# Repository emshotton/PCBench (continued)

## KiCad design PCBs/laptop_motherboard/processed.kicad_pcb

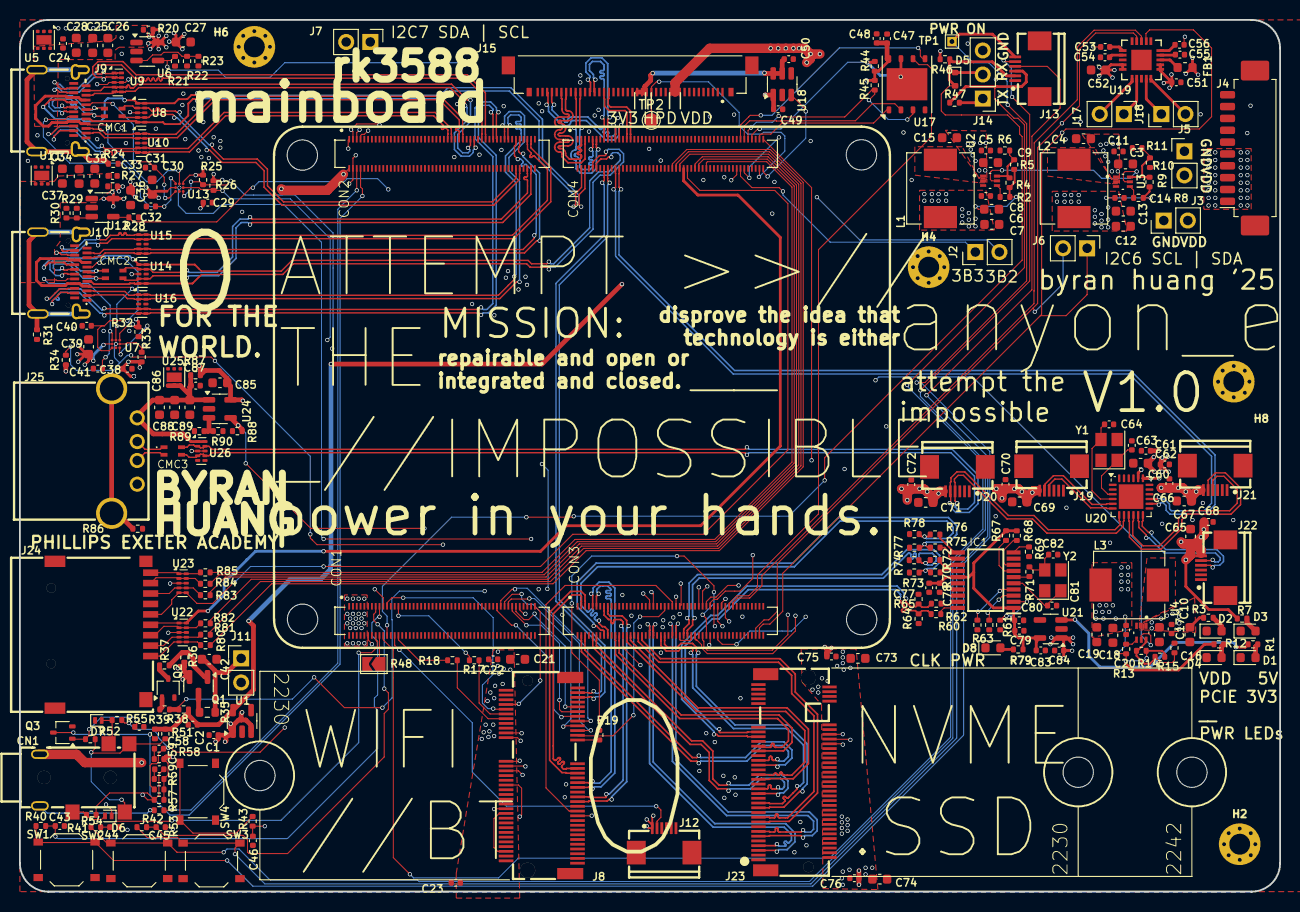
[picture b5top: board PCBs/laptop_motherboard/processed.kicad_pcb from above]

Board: 6 copper layers, 133.0 x 92.0 mm, 264 parts (0 on the bottom side), 236 nets.

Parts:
C1, C2, C22, C48, C49, C50, C53, C54, C55, C56, C57, C62, C75, C77, C79, C83, C84: 1uF; C_0402_1005Metric
C3, C4, C9, C10, C15, C16, C27, C28, C30, C36, C37, C39, C42, C52, C60, C65, C67, C69, C71, C85, C86: 10uF; C_0603_1608Metric
C5, C8, C11, C14, C17, C20, C29, C38, C78, C80: 100nF; C_0402_1005Metric
C6, C7, C12, C13, C18, C19, C21, C73, C74: 22uF; C_0603_1608Metric
C23, C47, C51, C58, C59, C61, C66, C68, C70, C72, C76: 0.1uF; C_0402_1005Metric
C24, C33, C87: 100nF (+25V); C_0402_1005Metric
C25, C26, C34, C35, C88, C89: 10uF (C913517); C_0603_1608Metric
C31, C32, C40, C41: 220pF; C_0402_1005Metric
C43, C44, C45, C46: 1nF; C_0402_1005Metric
C63, C64, C81, C82: 15pF; C_0402_1005Metric
CMC1, CMC2, CMC3: ACM2012; FIL_ACM2012-900-2P-T001
CN1: PJ-332A-6A (3.5mm Jack); AUDIO-SMD_PJ-332A-6A
D1: +3.3V LED; LED_0603_1608Metric
D2: VDD LED; LED_0603_1608Metric
D3: +5V LED; LED_0603_1608Metric
D4: PCIE LED; LED_0603_1608Metric
D5: LRB521S-30T1G; D_SOD-523
D6, D7: LESD8D5.0CB1T5G; D_SOD-882
D8: PI6C LED; LED_0603_1608Metric
FB1: GZ1608D601TF; L_0603_1608Metric
H1, H3, H5, H7: Hirose; Blank
H2, H4, H6, H8: M2; MountingHole_2.2mm_M2_Pad_Via
IC1: PI6C557-05BLE; SOP65P640X120-20N
J1: CM3588 Hirose Connector; CM3588
J2, J6, J7: EXT GPIO; PinHeader_1x02_P2.54mm_Vertical
J3: VDD EXT; PinHeader_1x02_P2.54mm_Vertical
J4: BATTERY IN; Molex_PicoBlade_53261-1071_1x10-1MP_P1.25mm_Horizontal
J5: VDD EXT 2; PinHeader_1x02_P2.54mm_Vertical
J8: Bus_M.2_Socket_E; CONN-SMD_APCI0147-P001A
J9: Outer USB-C; USB-C-SMD_TYPE-C-24P-QT
J10: USB_C_Receptacle; USB-C-SMD_TYPE-C-24P-QT
J11: 5V FAN; PinHeader_1x02_P2.54mm_Vertical
J12: HALL SWITCH; FPC-SMD_6P-P0.50_XUNPU_FPC-05F-6PH20
J13: SYSTEM; FPC-SMD_6P-P0.50_XUNPU_FPC-05F-6PH20
J14: DEBUG UART; PinHeader_1x03_P2.54mm_Vertical
J15: 20455-040E-76 OLED IPEX; IPEX_20455-040E-76
J17: LEFT SPEAKERS; PinHeader_1x02_P2.54mm_Vertical
J18: RIGHT SPEAKERS; PinHeader_1x02_P2.54mm_Vertical
J19, J20, J21, J22: USB; FPC-SMD_6P-P0.50_XUNPU_FPC-05F-6PH20
J23: Bus_M.2_Socket_M; CONN-SMD_AS0BC21-S30BM-7H
J24: Micro_SD_Card_Det1; TF-SMD_TF-CARD-H1.8
J25: USB-231-ARY; USB-A-TH_USB-231-ARY
L1, L3: MWSA0603S-3R3MT; L_Sunlord_MWSA0603S
L2: FXL0630-4R7-M; L_Sunlord_MWSA0603S
Q1: AO3415A; SOT-23
Q2, Q3: 2SK3018W; SOT-323_SC-70
R1, R2, R6, R7, R8, R12, R13, R16, R34, R38, R44, R45, R46, R52, R56, R57, R67, R68: 10k; R_0402_1005Metric
R3, R11, R79: 33k; R_0402_1005Metric
R4, R14: 49.9k; R_0402_1005Metric
R5, R15: 510k; R_0402_1005Metric
R9: 220k; R_0402_1005Metric
R10: 330k; R_0402_1005Metric
R17, R18, R20, R27, R53, R54, R55, R61, R63, R87: 0R; R_0402_1005Metric
R19, R25, R26, R32, R33, R50: 2.2k; R_0402_1005Metric
R21, R28, R51, R88: 100k; R_0402_1005Metric
R22, R23, R29, R30, R89, R90: 6.8k; R_0402_1005Metric
R24, R31, R86: 1M; R_0402_1005Metric
R35: 2.2R; R_0603_1608Metric
R36, R69: 470R; R_0402_1005Metric
R37: 1k; R_0402_1005Metric
R39, R40, R41, R42, R43, R71: 100R; R_0402_1005Metric
R47, R58, R59, R60, R62, R70, R72, R75, R76, R80, R81, R82, R83, R84, R85: 33R; R_0402_1005Metric
R48: 0R; SolderJumper-2_P1.3mm_Open_TrianglePad1.0x1.5mm
R64, R65, R73, R74, R77, R78: 49.9R; R_0402_1005Metric
R66: 4.7k; R_0402_1005Metric
SW1: PWR; SW_Push_1P1T_XKB_TS-1187A
SW2: RESET; SW_Push_1P1T_XKB_TS-1187A
SW3: MASK; SW_Push_1P1T_XKB_TS-1187A
SW4: RECOVERY; SW_Push_1P1T_XKB_TS-1187A
TP1: PWRON; TestPoint_THTPad_1.0x1.0mm_Drill0.5mm
TP2: HPD; TestPoint_Pad_D1.5mm
U1: RT9193-18GB; SOT-23-5
U2, U3, U4: TPS564257DRLR; SOT50P160X60-6N
U5, U11, U25: TVS2200DRV; WSON-6-1EP_2x2mm_P0.65mm_EP1x1.6mm
U6, U12, U24: SY6280AAC; SOT-23-5
U7, U13: FUSB302BUCX; WLCSP9_1P2X1P2_ONS
U8, U9, U10, U14, U15, U16, U22, U23, U26: TPD4E02B04; USON-10_2.5x1.0mm_P0.5mm
U17: SPI Flash; WSON-8-1EP_6x5mm_P1.27mm_EP3.4x4.3mm
U18: TPS22917DBV; SOT-23-6
U19: TPA2016D2RTJR; QFN50P400X400X80-21N
U20: CH334F; QFN-24-1EP_4x4mm_P0.5mm_EP2.6x2.6mm
U21: AP2127K-3.3; SOT-23-5
Y1: 12MHz; Crystal_SMD_3225-4Pin_3.2x2.5mm
Y2: 25MHz; Crystal_SMD_3225-4Pin_3.2x2.5mm

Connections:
+1V8: C2.1, C47.1, C48.1, R38.1, R44.1, R45.1, R50.2, R51.2, U1.5 (VOUT), U17.8 (VCC)
+3.3V: C1.1, C6.1, C7.1, C8.1, C29.1, C38.1, C49.1, C60.1, C61.1, L1.2, R1.2, R2.2, R4.2, R5.2, R25.1, R26.1, R32.1, R33.1, R34.1, R46.2, U1.1 (VIN), U1.3 (EN), U7.A3 (VDD), U13.A3 (VDD), U18.1 (VIN), U20.20 (VDD33), U21.3 (EN)
+3.3V_PCIE: C18.1, C19.1, C20.1, C21.1, C22.1, C23.1, C73.1, C74.1, C75.1, C76.1, J8.2 (3.3V), J8.4 (3.3V), J8.72 (3.3V), J8.74 (3.3V), J12.1, J23.2 (3.3V), J23.4 (3.3V), J23.12 (3.3V), J23.14 (3.3V), J23.16 (3.3V), J23.18 (3.3V), J23.70 (3.3V), J23.72 (3.3V), J23.74 (3.3V), L3.2, R12.2, R13.2, R14.2, R15.2
+5V: C12.1, C13.1, C14.1, C27.1, C30.1, C36.1, C39.1, C51.1, C52.1, C62.1, C65.1, C66.1, C67.1, C68.1, C69.1, C70.1, C71.1, C72.1, C84.1, C85.1, FB1.1, J19.6, J20.6, J21.6, J22.6, L2.2, Q1.2 (S), R7.2, R8.2, R9.2, R20.1, R27.1, R36.1, R87.1, U6.5 (IN), U7.B1 (VCONN), U12.5 (IN), U13.B1 (VCONN), U19.4 (PVDDL_2), U19.5 (PVDDL), U19.11 (PVDDR_2), U19.12 (PVDDR), U20.19 (V5), U21.1 (VIN), U24.5 (IN)
/3V3_SW: L1.1, U2.2 (SW)
/5V_SW: L2.1, U3.2 (SW)
/Audio/L_AUDIO: C53.1, C58.1, J1.104, R55.2, R56.2
/Audio/L_DET: CN1.5, CN1.6, R51.1, R52.2
/Audio/L_HP: CN1.4, D7.2 (A2), R55.1
/Audio/MIC: CN1.1, R53.1
/Audio/R_AUDIO: C56.1, C59.1, J1.103, R54.2, R57.2
/Audio/R_HP: CN1.3, D6.2 (A2), R54.1
/BOOT_SARADC_IN0: C45.1, J1.15, R42.1
/Ext_USB2.0/EXTUSB20_D3_N: CMC3.4, J20.5, U26.2 (D1-), U26.9 (NC)
/Ext_USB2.0/EXTUSB20_D3_P: CMC3.3, J20.4, U26.4 (D2+), U26.7 (NC)
/Ext_USB2.0/USB_N: CMC3.1, J25.2 (D-)
/Ext_USB2.0/USB_P: CMC3.2, J25.3 (D+)
/Ext_USB2.0/VBUS: C86.1, C87.1, C88.1, C89.1, J25.1 (VBUS), R87.2, U24.1 (OUT), U25.4 (IN), U25.5 (IN), U25.6 (IN), U26.1 (D1+), U26.10 (NC)
/GPIO0_A4/SDMMC_DET_L: J1.370, R85.1
/GPIO0_B2: J1.247, J8.21 (~SDIO_WAKE)
/GPIO0_C4/UART0_RX_M0: J1.270, R19.1
/GPIO0_C5/UART0_TX_M0/PWM4_M0: J1.272, J8.20 (~UART_WAKE)
/GPIO0_D3/CC_INT_L: J1.264, U13.B2 (INT_N)
/GPIO0_D5: J1.268, R34.2, U7.B2 (INT_N)
/GPIO1_A0/UART6_RX_M1: J1.273, J8.22 (UART_RXD)
/GPIO1_A1/UART6_TX_M1: J1.275, J8.32 (UART_TXD)
/GPIO1_A2/I2C4_SDA_M3_TP: J1.277, J8.36 (UART_RTS)
/GPIO1_A3/I2C4_SCL_M3_TP: J1.279, J8.34 (UART_CTS)
/GPIO1_A4: J1.281, U17.6 (SCK)
/GPIO1_A7: J1.283, U19.18 (SDZ)
/GPIO1_B0: J1.276, R88.1, U24.4 (ON)
/GPIO1_C4/HP_DET_L: J1.108, Q3.3 (D), R50.1
/GPIO1_D2/TYPEC5V_PWREN_H: J1.239, R21.1, U6.4 (ON)
/GPIO1_D3/PWM1_M1: J1.241, R38.2, R39.1
/GPIO2_A6: J1.79, J8.13 (SDIO_DATA0)
/GPIO2_A7: J1.81, J8.15 (SDIO_DATA1)
/GPIO2_B0: J1.83, J8.17 (SDIO_DATA2)
/GPIO2_B1: J1.85, J8.19 (SDIO_DATA3)
/GPIO2_B2: J1.87, J8.11 (SDIO_CMD)
/GPIO2_B3: J1.89, J8.9 (SDIO_CLK)
/GPIO2_B7: J1.99, J8.8 (PCM_CLK/I2S_SCK)
/GPIO2_C0: J1.21, J8.10 (PCM_SYNC/I2S_WS)
/GPIO2_C3: J1.27, R17.2
/GPIO3_A0/SPI4_MISO_M1/PWM10_M0: J1.387, U17.5 (SI/IO0)
/GPIO3_A1/SPI4_MOSI_M1: J1.389, U17.2 (SO/IO1)
/GPIO3_A2/SPI4_CLK_M1/UART8_TX_M1: J1.391, R45.2, U17.3 (~WP/IO2)
/GPIO3_A3/SPI4_CS0_M1/UART8_RX_M1: J1.393, R44.2, U17.7 (~HOLD/IO3)
/GPIO3_A5: J1.397, U17.1 (~CS)
/GPIO3_A6/LCD_RST: J1.399, J8.42 (VENDOR_DEFINED)
/GPIO3_A7: J1.400, U18.3 (ON)
/GPIO3_B2: J1.386, J2.2
/GPIO3_B3: J1.388, J2.1
/GPIO3_B4: J1.390, R28.1, U12.4 (ON)
/GPIO3_B7: J1.398, J15.16, TP2.1
/GPIO4_A0/TP_2_INT_L: J1.251, J8.53 (~CLKREQ0)
/GPIO4_A1/TP_2_RST_L: J1.253, J8.55 (~PEWAKE0)
/GPIO4_A2: J1.255, J8.52 (~PERST0)
/GPIO4_B4/PCIE30X4_CLKREQn_M1_L: J1.265, J23.52 (~CLKREQ)
/GPIO4_B5/PCIE30X4_WAKEn_M1_L: J1.267, J23.54 (~PEWAKE)
/GPIO4_B6/PCIE30X4_PERSTn_M1_L: J1.269, J23.50 (~PERST)
/GPIO4_C2: J1.26, J12.2
/GPIO4_C3: J1.28, R18.2
/HDMI1_TX0N: J1.317, J15.29
/HDMI1_TX0P: J1.315, J15.28
/HDMI1_TX1N: J1.311, J15.32
/HDMI1_TX1P: J1.309, J15.31
/HDMI1_TX2N: J1.305, J15.35
/HDMI1_TX2P: J1.303, J15.34
/HDMI1_TX3N: J1.323, J15.38
/HDMI1_TX3P: J1.321, J15.37
/HDMI1_TX_SBDN: J1.329, J15.25
/HDMI1_TX_SBDP: J1.327, J15.26
/I2C6_SCL_M0: J1.296, J6.2, R26.2, U13.B3 (SCL), U19.19 (SDA)
/I2C6_SDA_M0: J1.298, J6.1, R25.2, U13.C3 (SDA), U19.17 (SCL)
/I2C7_SCL_M0: J1.107, J7.1, R33.2, U7.B3 (SCL)
/I2C7_SDA_M0: J1.105, J7.2, R32.2, U7.C3 (SDA)
/MIC_IN: J1.106, R53.2
/PCIE2.0-EKEY/GPIO3_D5/PWM11_M3/LCD_2_BL: J8.54 (~W_DISABLE2), J8.70 (UIM_POWER_SRC/GPIO1/~PEWAKE1)
/PCIE3.0-MKEY/+3.3V_PI6C: C77.1, C78.1, C79.1, C80.1, C83.1, IC1.1 (VDDXD), IC1.15 (VDDODA), R67.1, R68.1, R79.2, U21.5 (VOUT)
/PCIE3.0-MKEY/CLK2N: IC1.13 (~CLK2), R72.1
/PCIE3.0-MKEY/CLK2P: IC1.14 (CLK2), R70.1
/PCIE3.0-MKEY/CLK3N: IC1.11 (~CLK3), R76.1
/PCIE3.0-MKEY/CLK3P: IC1.12 (CLK3), R75.1
/PCIE3.0-MKEY/PCIE30_REFCLK_A_N: J23.53 (REFCLKn), R62.2, R65.2
/PCIE3.0-MKEY/PCIE30_REFCLK_A_P: J23.55 (REFCLKp), R60.2, R64.2
/PCIE3.0-MKEY/X1: C81.1, IC1.5 (X1), Y2.1
/PCIE3.0-MKEY/X2: IC1.6 (X2), R71.1
/PCIE20_1_REFCLKN: J1.217, J8.49 (REFCLKn0)
/PCIE20_1_REFCLKP: J1.215, J8.47 (REFCLKp0)
/PCIE20_1_RXN: J1.211, J8.41 (PERp0)
/PCIE20_1_RXP: J1.209, J8.43 (PERn0)
/PCIE20_1_TXN: J1.205, J8.37 (PETn0)
/PCIE20_1_TXP: J1.203, J8.35 (PETp0)
/PCIE30_PORT0_REFCLKN: J1.218, R76.2, R78.2
/PCIE30_PORT0_REFCLKP: J1.216, R75.2, R77.2
/PCIE30_PORT0_RX0N: J1.206, J23.41 (PERn0/SATA-B+)
/PCIE30_PORT0_RX0P: J1.204, J23.43 (PERp0/SATA-B-)
/PCIE30_PORT0_RX1N: J1.212, J23.29 (PERn1)
/PCIE30_PORT0_RX1P: J1.210, J23.31 (PERp1)
/PCIE30_PORT0_TX0N: J1.224, J23.47 (PETn0/SATA-A-)
/PCIE30_PORT0_TX0P: J1.222, J23.49 (PETp0/SATA-A+)
/PCIE30_PORT0_TX1N: J1.230, J23.35 (PETn1)
/PCIE30_PORT0_TX1P: J1.228, J23.37 (PETp1)
/PCIE30_PORT1_REFCLKN: J1.260, R72.2, R74.2
/PCIE30_PORT1_REFCLKP: J1.258, R70.2, R73.2
/PCIE30_PORT1_RX2N: J1.236, J23.17 (PERn2)
/PCIE30_PORT1_RX2P: J1.234, J23.19 (PERp2)
/PCIE30_PORT1_RX3N: J1.242, J23.5 (PERn3)
/PCIE30_PORT1_RX3P: J1.240, J23.7 (PERp3)
/PCIE30_PORT1_TX2N: J1.248, J23.23 (PETn2)
/PCIE30_PORT1_TX2P: J1.246, J23.25 (PETp2)
/PCIE30_PORT1_TX3N: J1.254, J23.11 (PETn3)
/PCIE30_PORT1_TX3P: J1.252, J23.13 (PETp3)
/PCIE_SW: L3.1, U4.2 (SW)
/PMIC_EXT_EN_OUT: J1.19, U2.5 (EN), U3.5 (EN), U4.5 (EN)
/PWRON_L: C43.1, J1.17, R40.1
/RECOVERY: C46.1, J1.101, R43.1
/RESET_L: C44.1, J1.16, R41.1
/SD Card/CLK: J1.360, J24.5 (CLK), U23.5 (D2-), U23.6 (NC)
/SD Card/CMD: J24.3 (CMD), R82.2, U22.2 (D1-), U22.9 (NC)
/SD Card/D0: J24.7 (DAT0), R83.2, U23.4 (D2+), U23.7 (NC)
/SD Card/D1: J24.8 (DAT1), R84.2, U23.2 (D1-), U23.9 (NC)
/SD Card/D2: J24.1 (DAT2), R80.2, U22.5 (D2-), U22.6 (NC)
/SD Card/D3: J24.2 (DAT3/CD), R81.2, U22.4 (D2+), U22.7 (NC)
/SD Card/DET: J24.9 (DET), R85.2, U23.1 (D1+), U23.10 (NC)
/SD Card/VDD: J1.358, J24.4 (VDD), U22.1 (D1+), U22.10 (NC)
/SDMMC0_CMD: J1.356, R82.1
/SDMMC0_D0: J1.364, R83.1
/SDMMC0_D1: J1.366, R84.1
/SDMMC0_D2: J1.352, R80.1
/SDMMC0_D3: J1.354, R81.1
/System/BOOT_SARADC: J13.4, R42.2, SW3.1 (A)
/System/PWRON_L_IN: J13.6, R40.2, SW1.1 (A), TP1.1
/System/RECOVERY_IN: R43.2, SW4.1 (A)
/System/RESET_L_IN: J13.5, R41.2, SW2.1 (A)
/System/UART_RX: D5.2 (A), J1.22, J13.2, R46.1
/System/UART_TX: J1.20, J13.3, R47.1
/USB2.0/D1_N: J22.5, U20.11 (DM1)
/USB2.0/D1_P: J22.4, U20.12 (DP1)
/USB2.0/D2_N: J21.5, U20.9 (DM2)
/USB2.0/D2_P: J21.4, U20.10 (DP2)
/USB2.0/D4_N: J19.5, U20.5 (DM4)
/USB2.0/D4_P: J19.4, U20.6 (DP4)
/USB2.0/X1: C63.1, U20.3 (XO), Y1.1
/USB2.0/X2: C64.1, U20.4 (XI), Y1.3
/USB20_HOST0_DN: J1.324, U20.14 (DMU)
/USB20_HOST0_DP: J1.322, U20.15 (DPU)
/USB20_HOST1_DN: J1.318, J8.5 (USB_D-)
/USB20_HOST1_DP: J1.316, J8.3 (USB_D+)
/USBC0/CC1: C31.1, J9.A5 (CC1), U13.C1 (CC1)
/USBC0/CC2: C32.1, J9.B5 (CC2), U13.A1 (CC2)
/USBC0/D+: CMC1.4, J1.190, U8.2 (D1-), U8.9 (NC)
/USBC0/D-: CMC1.3, J1.192, U8.4 (D2+), U8.7 (NC)
/USBC0/IN_D+: CMC1.1, J9.A6 (D+), J9.B6 (D+)
/USBC0/IN_D-: CMC1.2, J9.A7 (D-), J9.B7 (D-)
/USBC0/RX1+: J1.171, J9.B11 (RX1+), U9.1 (D1+), U9.10 (NC)
/USBC0/RX1-: J1.173, J9.B10 (RX1-), U9.2 (D1-), U9.9 (NC)
/USBC0/RX2+: J1.159, J9.A11 (RX2+), U10.2 (D1-), U10.9 (NC)
/USBC0/RX2-: J1.161, J9.A10 (RX2-), U10.1 (D1+), U10.10 (NC)
/USBC0/SBUS+: J1.304, J9.A8 (SBU1), U8.5 (D2-), U8.6 (NC)
/USBC0/SBUS-: J1.306, J9.B8 (SBU2), U8.1 (D1+), U8.10 (NC)
/USBC0/TX1+: J1.165, J9.A2 (TX1+), U9.4 (D2+), U9.7 (NC)
/USBC0/TX1-: J1.167, J9.A3 (TX1-), U9.5 (D2-), U9.6 (NC)
/USBC0/TX2+: J1.153, J9.B2 (TX2+), U10.5 (D2-), U10.6 (NC)
/USBC0/TX2-: J1.155, J9.B3 (TX2-), U10.4 (D2+), U10.7 (NC)
/USBC0/VBUS: C24.1, C25.1, C26.1, C28.1, J9.A4 (VBUS), J9.A9 (VBUS), J9.B4 (VBUS), J9.B9 (VBUS), R20.2, U5.4 (IN), U5.5 (IN), U5.6 (IN), U6.1 (OUT), U13.A2 (VBUS)
/USBC1/CC1: C40.1, J10.A5 (CC1), U7.C1 (CC1)
/USBC1/CC2: C41.1, J10.B5 (CC2), U7.A1 (CC2)
/USBC1/D+: CMC2.4, J1.196, U14.2 (D1-), U14.9 (NC)
/USBC1/D-: CMC2.3, J1.198, U14.4 (D2+), U14.7 (NC)
/USBC1/IN_D+: CMC2.1, J10.A6 (D+), J10.B6 (D+)
/USBC1/IN_D-: CMC2.2, J10.A7 (D-), J10.B7 (D-)
/USBC1/RX1+: J1.195, J10.B11 (RX1+), U15.1 (D1+), U15.10 (NC)
/USBC1/RX1-: J1.197, J10.B10 (RX1-), U15.2 (D1-), U15.9 (NC)
/USBC1/RX2+: J1.183, J10.A11 (RX2+), U16.2 (D1-), U16.9 (NC)
/USBC1/RX2-: J1.185, J10.A10 (RX2-), U16.1 (D1+), U16.10 (NC)
/USBC1/SBUS+: J1.310, J10.A8 (SBU1), U14.5 (D2-), U14.6 (NC)
/USBC1/SBUS-: J1.312, J10.B8 (SBU2), U14.1 (D1+), U14.10 (NC)
/USBC1/TX1+: J1.189, J10.A2 (TX1+), U15.4 (D2+), U15.7 (NC)
/USBC1/TX1-: J1.191, J10.A3 (TX1-), U15.5 (D2-), U15.6 (NC)
/USBC1/TX2+: J1.177, J10.B2 (TX2+), U16.5 (D2-), U16.6 (NC)
/USBC1/TX2-: J1.179, J10.B3 (TX2-), U16.4 (D2+), U16.7 (NC)
/USBC1/VBUS: C33.1, C34.1, C35.1, C37.1, J10.A4 (VBUS), J10.A9 (VBUS), J10.B4 (VBUS), J10.B9 (VBUS), R27.2, U7.A2 (VBUS), U11.4 (IN), U11.5 (IN), U11.6 (IN), U12.1 (OUT)
/VDC_MODE: J1.18, R48.1
/eDP/VCC_3.3V: C50.1, J15.17, J15.18, J15.19, U18.5 (QOD), U18.6 (VOUT)
GND: C1.2, C2.2, C3.2, C4.2, C5.2, C6.2, C7.2, C8.2, C9.2, C10.2, C11.2, C12.2, C13.2, C14.2, C15.2, C16.2, C17.2, C18.2, C19.2, C20.2, C21.2, C22.2, C23.2, C24.2, C25.2, C26.2, C27.2, C28.2, C29.2, C30.2, C31.2, C32.2, C33.2, C34.2, C35.2, C36.2, C37.2, C38.2, C39.2, C40.2, C41.2, C42.2, C43.2, C44.2, C45.2, C46.2, C47.2, C48.2, C49.2, C50.2, C51.2, C52.2, C54.1, C55.1, C57.2, C60.2, C61.2, C62.2, C63.2, C64.2, C65.2, C66.2, C67.2, C68.2, C69.2, C70.2, C71.2, C72.2, C73.2, C74.2, C75.2, C76.2, C77.2, C78.2, C79.2, C80.2, C81.2, C82.2, C83.2, C84.2, C85.2, C86.2, C87.2, C88.2, C89.2, D1.1 (K), D2.1 (K), D3.1 (K), D4.1 (K), D6.1 (A1), D7.1 (A1), D8.1 (K), IC1.9 (GNDXD), IC1.16 (GNDODA), J1.11, J1.12, J1.13, J1.24, J1.33, J1.34, J1.39, J1.40, J1.45, J1.46, J1.51, J1.52, J1.57, J1.58, J1.63, J1.64, J1.69, J1.70, J1.73, J1.76, J1.77, J1.82, J1.88, J1.91, J1.94, J1.100, J1.109, J1.110, J1.115, J1.116, J1.121, J1.122, J1.127, J1.128, J1.133, J1.134, J1.139, J1.140, J1.145, J1.146, J1.151, J1.152, J1.157, J1.158, J1.163, J1.164, J1.169, J1.170, J1.175, J1.176, J1.181, J1.182, J1.187, J1.188, J1.193, J1.194, J1.199, J1.200, J1.201, J1.202, J1.207, J1.208, J1.213, J1.214, J1.219, J1.220, J1.225, J1.226, J1.231, J1.232, J1.237, J1.238, J1.244, J1.249, J1.250, J1.256, J1.259, J1.262, J1.271, J1.284, J1.285, J1.294, J1.301, J1.302, J1.307, J1.308, J1.313, J1.314, J1.319, J1.320, J1.325, J1.326, J1.331, J1.332, J1.337, J1.338, J1.343, J1.344, J1.349, J1.350, J1.355, J1.361, J1.362, J1.368, J1.380, J1.383, J1.396, J3.1, J4.6, J4.7, J4.8, J4.9, J4.10, J4.MP (MountPin), J5.1, J8.1 (GND), J8.7 (GND), J8.18 (GND), J8.33 (GND), J8.39 (GND), J8.45 (GND), J8.51 (GND), J8.57 (GND), J8.63 (GND), J8.69 (GND), J8.75 (GND), J9.A1 (GND), J9.A12 (GND), J9.B1 (GND), J9.B12 (GND), J10.A1 (GND), J10.A12 (GND), J10.B1 (GND), J10.B12 (GND), J11.2, J12.3, J12.MP (MountPin), J13.1, J13.MP (MountPin), J14.3, J15.14, J15.15, J15.21, J15.22, J15.23, J15.24, J15.27, J15.30, J15.33, J15.36, J15.39, J15.S1 (SHIELD), J15.S2 (SHIELD), J15.S3 (SHIELD), J15.S4 (SHIELD), J19.1, J19.MP (MountPin), J20.1, J20.MP (MountPin), J21.1, J21.MP (MountPin), J22.1, J22.MP (MountPin), J23.1 (GND), J23.3 (GND), J23.9 (GND), J23.15 (GND), J23.21 (GND), J23.27 (GND), J23.33 (GND), J23.39 (GND), J23.45 (GND), J23.51 (GND), J23.57 (GND), J23.71 (GND), J23.73 (GND), J23.75 (GND), J24.6 (VSS), J24.10 (SHIELD), J25.4 (GND), Q2.2 (S), Q3.2 (S), R6.1, R10.1, R11.1, R16.1, R21.2, R22.2, R23.2, R24.2, R28.2, R29.2, R30.2, R31.2, R48.2, R61.1, R63.1, R64.1, R65.1, R66.1, R69.1, R73.1, R74.1, R77.1, R78.1, R86.2, R88.2, R89.2, R90.2, SW1.2 (B), SW2.2 (B), SW3.2 (B), SW4.2 (B), U1.2 (GND), U2.3 (GND), U3.3 (GND), U4.3 (GND), U5.1 (GND), U5.2 (GND), U5.3 (GND), U5.7 (GND), U6.2 (GND), U7.C2 (GND), U8.3 (GND), U8.8 (GND), U9.3 (GND), U9.8 (GND), U10.3 (GND), U10.8 (GND), U11.1 (GND), U11.2 (GND), U11.3 (GND), U11.7 (GND), U12.2 (GND), U13.C2 (GND), U14.3 (GND), U14.8 (GND), U15.3 (GND), U15.8 (GND), U16.3 (GND), U16.8 (GND), U17.4 (GND), U18.2 (GND), U19.3 (AGND), U19.8 (PGND), U19.21 (EP), U20.24 (PWREN#), U20.25 (GND), U21.2 (GND), U22.3 (GND), U22.8 (GND), U23.3 (GND), U23.8 (GND), U24.2 (GND), U25.1 (GND), U25.2 (GND), U25.3 (GND), U25.7 (GND), U26.3 (GND), U26.8 (GND), Y1.2, Y1.4, Y2.2, Y2.4
GND_AUDUO: CN1.2, J1.102, R56.1, R57.1, R58.1, R59.1
unnamed: C58.2, R58.2
unnamed: C59.2, R59.2
unnamed: C82.1, R71.2, Y2.3
unnamed: D1.2 (A), R1.1
unnamed: D2.2 (A), R3.1
unnamed: D3.2 (A), R7.1
unnamed: D4.2 (A), R12.1
unnamed: D5.1 (K), J14.2
unnamed: D8.2 (A), R79.1
unnamed: IC1.20 (CLK0), R60.1
unnamed: IC1.10 (IREF), R69.2
unnamed: IC1.8 (OE), R68.2
unnamed: IC1.2 (S0), R61.2
unnamed: IC1.3 (S1), R63.2
unnamed: IC1.4 (S2), R66.2
unnamed: IC1.19 (~CLK0), R62.1
unnamed: IC1.7 (~PD), R67.2
unnamed: J8.12 (PCM_IN/I2S_SD_IN), R17.1
unnamed: J8.14 (PCM_OUT/I2S_SD_OUT), R18.1
unnamed: J8.23 (~SDIO_RESET), R19.2
unnamed: J9.S1 (SHIELD), R24.1
unnamed: J10.S1 (SHIELD), R31.1
unnamed: C42.1, J11.1, R35.2
unnamed: J14.1, R47.2
unnamed: J17.1, U19.7 (OUTL-)
unnamed: J17.2, U19.6 (OUTL+)
unnamed: J18.1, U19.9 (OUTR-)
unnamed: J18.2, U19.10 (OUTR+)
unnamed: J25.5 (Shield), R86.1
unnamed: Q1.3 (D), R35.1
unnamed: Q1.1 (G), R36.2, R37.1
unnamed: Q2.3 (D), R37.2
unnamed: Q2.1 (G), R39.2
unnamed: C57.1, Q3.1 (G), R52.1
unnamed: R4.1, R5.1, R6.2, U2.6 (FB)
unnamed: R2.1, U2.4 (PG)
unnamed: R9.1, R10.2, R11.2, U3.6 (FB)
unnamed: R8.1, U3.4 (PG)
unnamed: R14.1, R15.1, R16.2, U4.6 (FB)
unnamed: R13.1, U4.4 (PG)
unnamed: R22.1, R23.1, U6.3 (ISET)
unnamed: R29.1, R30.1, U12.3 (ISET)
unnamed: FB1.2, U19.13 (AVDD)
unnamed: C53.2, U19.1 (INL+)
unnamed: C54.2, U19.2 (INL-)
unnamed: C56.2, U19.15 (INR+)
unnamed: C55.2, U19.14 (INR-)
unnamed: R89.1, R90.1, U24.3 (ISET)
VDD: C3.1, C4.1, C5.1, C9.1, C10.1, C11.1, C15.1, C16.1, C17.1, J1.1, J1.2, J1.3, J1.4, J1.5, J1.6, J1.7, J1.8, J1.9, J1.10, J3.2, J4.1, J4.2, J4.3, J4.4, J4.5, J5.2, J15.10, J15.11, J15.12, R3.2, U2.1 (VIN), U3.1 (VIN), U4.1 (VIN)

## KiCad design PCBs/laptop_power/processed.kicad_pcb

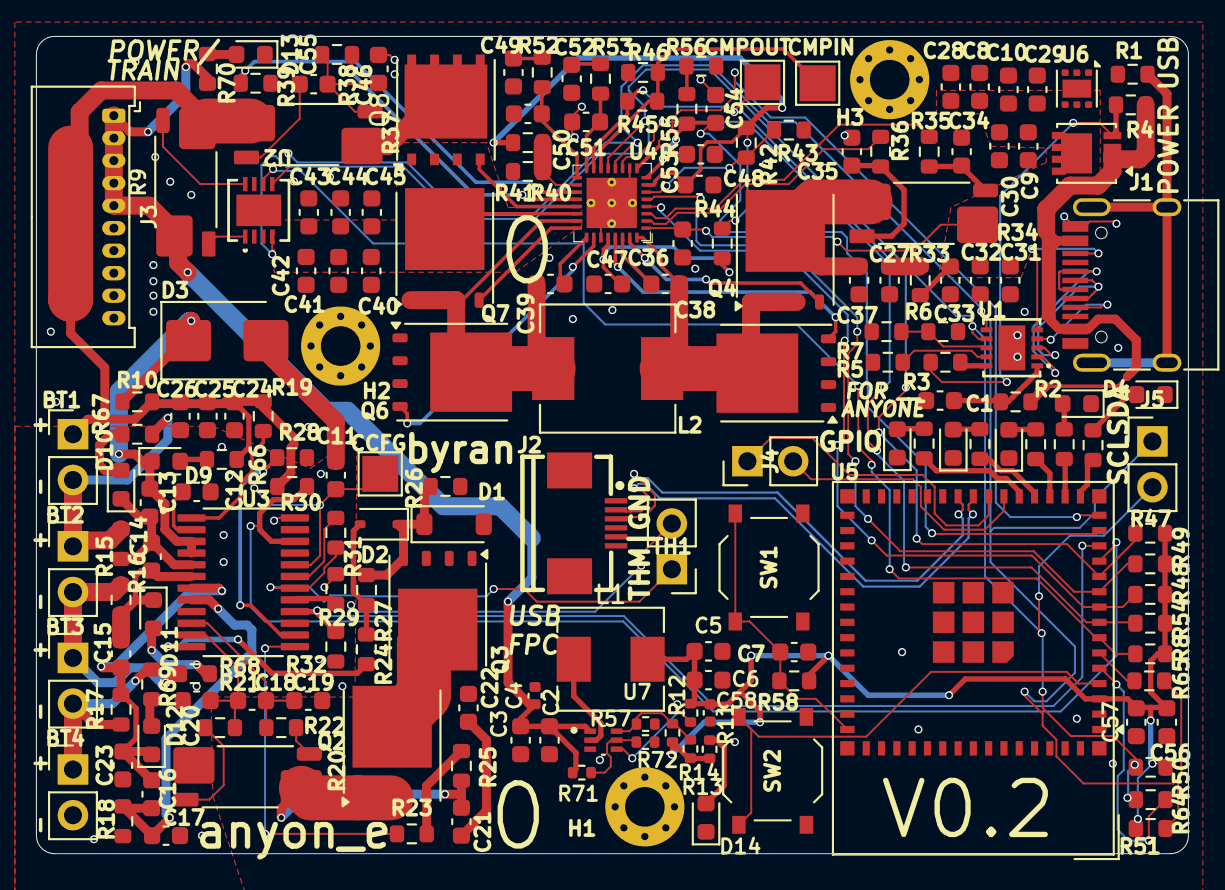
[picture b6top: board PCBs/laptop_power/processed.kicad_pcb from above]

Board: 13 copper layers, 64.0 x 45.4 mm, 179 parts (0 on the bottom side), 115 nets.

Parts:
BT1: Cell 1; PinHeader_1x02_P2.54mm_Vertical
BT2: Cell 2; PinHeader_1x02_P2.54mm_Vertical
BT3: Cell 3; PinHeader_1x02_P2.54mm_Vertical
BT4: Cell 4; PinHeader_1x02_P2.54mm_Vertical
C1, C7, C11, C12, C13, C14, C15, C16, C17, C23, C27, C46, C48: 1uF; C_0603_1608Metric
C2, C3, C8, C9, C24, C25, C28, C29, C30, C31, C32, C33, C40, C41, C42, C43, C44, C45, C56: 10uF; C_0603_1608Metric
C4, C58: 100nF; C_0402_1005Metric
C5, C6: 22uF; C_0603_1608Metric
C10, C26: 100nF; C_0603_1608Metric
C18, C19, C20, C21, C22, C55, C57: 0.1uF; C_0603_1608Metric
C34, C35: 33nF; C_0603_1608Metric
C36: 470nF; C_0603_1608Metric
C37: 10nF; C_0603_1608Metric
C38, C39: 47nF; C_0603_1608Metric
C47: 2.2uF; C_0603_1608Metric
C49: 680pF; C_0603_1608Metric
C50: 15pF; C_0603_1608Metric
C51: 33pF; C_0603_1608Metric
C52: 1800pF; C_0603_1608Metric
C53, C54: 100pF; C_0603_1608Metric
D1: MMSZ5248B; D_SOD-123
D2: BAS316; D_SOD-323
D3: SMBJ26A-13-F; D_SMB
D4: LED1; LED_0603_1608Metric
D5: LED2; LED_0603_1608Metric
D6: LED3; LED_0603_1608Metric
D7: LED4; LED_0603_1608Metric
D8: LED5; LED_0603_1608Metric
D9: C4 LED; LED_0603_1608Metric
D10: C3 LED; LED_0603_1608Metric
D11: C2 LED; LED_0603_1608Metric
D12: C1 LED; LED_0603_1608Metric
D13: VDD LED; LED_0603_1608Metric
D14: +3.3V LED; LED_0603_1608Metric
H1, H2, H3: M2; MountingHole_2.2mm_M2_Pad_Via
J1: USB-C Power + USB2.0; USB_C_Receptacle_HRO_TYPE-C-31-M-12
J2: USB; FPC-SMD_6P-P0.50_XUNPU_FPC-05F-6PH20
J3: BATTERY OUT; Molex_PicoBlade_53048-1010_1x10_P1.25mm_Horizontal
J4: BACKUP; PinHeader_1x02_P2.54mm_Vertical
J5: I2C; PinHeader_1x02_P2.54mm_Vertical
L1: MWSA0503S-3R3MT; L_Sunlord_MWSA0503S
L2: MWSA0603S-2R2MT; L_Sunlord_MWSA0603S
Q1: SI7617DN-T1-GE3; Vishay_PowerPAK_1212-8_Single
Q2, Q3, Q4, Q5, Q6, Q7: CSD18534Q5A; TDSON-8-1
Q8: AON6411; AO_DFN-8-1EP_5.55x5.2mm_P1.27mm_EP4.12x4.6mm
R1, R27: 1M; R_0603_1608Metric
R2, R38, R39, R44: 10R; R_0603_1608Metric
R3, R23, R24: 5.1k; R_0603_1608Metric
R4: 49.9k; R_0603_1608Metric
R5, R6: DNP; R_0603_1608Metric
R7, R64, R65: 0R; R_0603_1608Metric
R8: 2.2k; R_0603_1608Metric
R9, R34, R37: 10mΩ SHUNT FMF25FPJR010-LH; R_Shunt_Vishay_WSK2512_6332Metric_T1.19mm
R10, R15, R16, R17, R18: 33R; R_0603_1608Metric
R11, R71: 47k; R_0402_1005Metric
R12, R57: 10k; R_0402_1005Metric
R13: 49.9k; R_0402_1005Metric
R14: 510k; R_0402_1005Metric
R19, R66, R67, R68, R69, R70: 1k; R_0603_1608Metric
R20: 15mΩ SHUNT RLP25FEER015; R_Shunt_Vishay_WSK2512_6332Metric_T1.19mm
R21, R22: 100R; R_0603_1608Metric
R25: 10M; R_0603_1608Metric
R26: 3M; R_0603_1608Metric
R28, R41: 470k; R_0603_1608Metric
R29: 100k; R_0603_1608Metric
R30, R31, R32, R47, R48, R49, R50, R51, R52, R58, R59, R60, R61, R62, R63: 10k; R_0603_1608Metric
R33: 2.2R; R_0603_1608Metric
R35, R36: 5.1R; R_0603_1608Metric
R40: 130k; R_0603_1608Metric
R42: 390k; R_0603_1608Metric
R43: 220k; R_0603_1608Metric
R45: 2M; R_0603_1608Metric
R46: 300k; R_0603_1608Metric
R53: 40.2k; R_0603_1608Metric
R54: 200R; R_0603_1608Metric
R55: 110k; R_0603_1608Metric
R56: 27k; R_0603_1608Metric
R72: 12k; R_0402_1005Metric
SW1: RST; SW_Push_1P1T_XKB_TS-1187A
SW2: BOOT; SW_Push_1P1T_XKB_TS-1187A
TH1: 103AT 10k; PinHeader_1x02_P2.54mm_Vertical
TP1: CCFG; TestPoint_Pad_2.0x2.0mm
TP2: CMPIN; TestPoint_Pad_2.0x2.0mm
TP3: CMPOUT; TestPoint_Pad_2.0x2.0mm
U1: HUSB238; DFN-10_L3.0-W3.0-P0.50-BL-EP2.5
U2: LTC2943; DFN-8_DD_LIT
U3: BQ7791501PWR; SOP65P640X120-24N
U4: BQ25713RSNR; RSN0032B
U5: ESP32-S3-MINI-1; ESP32-S2-MINI-1
U6: TVS2200DRV; WSON-6-1EP_2x2mm_P0.65mm_EP1x1.6mm
U7: TPS564257DRLR; SOT50P160X60-6N

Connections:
+3.3V: C5.1, C6.1, C56.2, C57.2, C58.1, L1.2, R8.2, R11.2, R12.2, R13.2, R14.2, R47.2, R48.2, R49.2, R50.2, R51.2, R54.2, R58.2, U5.3 (3V3)
/3V3_SW: L1.1, U7.2 (SW)
/BATDRV_N: Q8.4 (G), U4.21 (BATDRV_N)
/BMS_SRN: C18.1, C20.1, R21.2, U3.11 (SRN)
/BMS_SRP: C18.2, C19.1, R22.2, U3.10 (SRP)
/BTST1: C38.2, U4.30 (BTST1)
/BTST2: C39.2, U4.25 (BTST2)
/C1: BT3.2 (-), BT4.1 (+), R17.1, R69.1
/C2: BT2.2 (-), BT3.1 (+), R16.1, R68.1
/C3: BT1.2 (-), BT2.1 (+), R15.1, R67.1
/C4: BT1.1 (+), C24.1, C25.1, C26.1, R9.4, R10.1, R19.1, R30.2, R37.1, R66.1
/CBI: R32.1, U3.16 (CBI), U5.13 (IO9)
/CC1: J1.A5 (CC1), U1.4 (CC1)
/CC2: J1.B5 (CC2), U1.5 (CC2)
/CELL_BATPRES: R40.1, R41.2, U4.18 (CELL_BATPRES)
/CHG: Q2.4 (G), R23.2, R25.2
/CHRG_OK: R48.1, U4.4 (CHRG_OK), U5.9 (IO5)
/CMPOUT: R45.2, R47.1, TP3.1, U4.15 (CMPOUT), U5.11 (IO7)
/COMP1: C51.1, R53.2, U4.16 (COMP1)
/COMP2: C50.1, R52.2, U4.17 (COMP2)
/D+: J1.A6 (D+), J1.B6 (D+), U1.2 (D+)
/D-: J1.A7 (D-), J1.B7 (D-), U1.3 (D-)
/DSG: D1.1 (K), D2.1 (K), Q3.4 (G), R26.2, R27.2
/EN: C7.2, R58.1, SW1.1 (A), U5.45 (EN)
/EN_OTG: R49.1, U4.5 (EN_OTG), U5.10 (IO6)
/HIDRV1: Q4.4 (G), U4.31 (HIDRV1)
/HIDRV2: Q7.4 (G), U4.24 (HIDRV2)
/IADPT: C54.2, R55.2, U4.8 (IADPT), U5.14 (IO10)
/IBAT: C53.2, U4.9 (IBAT), U5.15 (IO11)
/ILIM_HIZ: R42.1, R43.2, U4.6 (ILIM_HIZ)
/IO0: SW2.1 (A), U5.4 (IO0)
/LD: R28.2, U3.14 (LD)
/LED1: R59.1, U5.16 (IO12)
/LED2: R60.1, U5.17 (IO13)
/LED3: R61.1, U5.18 (IO14)
/LED4: R62.1, U5.19 (IO15)
/LED5: R63.1, U5.20 (IO16)
/LODRV1: Q5.4 (G), U4.29 (LODRV1)
/LODRV2: Q6.4 (G), U4.26 (LODRV2)
/PRES: R30.1, U3.22 (PRES), U5.12 (IO8)
/PROCHOT_N: R54.1, U4.11 (PROCHOT_N), U5.8 (IO4)
/REGN: C47.1, R44.2, U4.28 (REGN)
/SCL: J5.2, R50.1, R64.2, U1.7 (SCL), U2.4 (SCL), U4.13 (SCL)
/SDA: J5.1, R51.1, R65.2, U1.6 (SDA), U2.5 (SDA), U4.12 (SDA)
/SRN: R39.1, U4.19 (SRN)
/SRP: R38.1, U4.20 (SRP)
/SW1: C38.1, L2.1, Q4.1 (S), Q4.2 (S), Q4.3 (S), Q5.5 (D), U4.32 (SW1)
/SW2: C39.1, L2.2, Q6.5 (D), Q7.1 (S), Q7.2 (S), Q7.3 (S), U4.23 (SW2)
/USB_D+: J2.3, U5.24 (IO20)
/USB_D-: J2.2, U5.23 (IO19)
/VBUS: C8.1, C9.1, C10.1, C28.1, C29.1, C30.1, C31.1, C32.1, C33.1, C36.1, Q1.5 (D), R33.2, R34.4, U4.1 (VBUS), U6.4 (IN), U6.5 (IN), U6.6 (IN)
/VC0: C16.2, C17.1, R18.2, U3.8 (VC0)
/VC1: C15.2, C16.1, C23.1, D12.1 (K), R17.2, U3.7 (VC1)
/VC2: C14.2, C15.1, D11.1 (K), R16.2, U3.6 (VC2)
/VC3: C13.2, C14.1, D10.1 (K), R15.2, U3.5 (VC3)
/VC4: C13.1, D3.1 (A1), D9.1 (K), R10.2, U3.3 (VC5), U3.4 (VC4)
/VDDA: C48.1, R40.2, R42.2, R44.1, U4.7 (VDDA)
/VSYS: C40.1, C41.1, C42.1, C43.1, C44.1, C45.1, Q7.5 (D), Q8.1 (S), Q8.2 (S), Q8.3 (S), U4.22 (VSYS)
/~ALCC: R8.1, U2.6 (*ALCC), U5.7 (IO3)
GND: C1.2, C2.2, C3.2, C4.2, C5.2, C6.2, C7.1, C8.2, C9.2, C10.2, C22.2, C27.2, C28.2, C29.2, C30.2, C31.2, C32.2, C33.2, C34.2, C35.2, C36.2, C37.2, C40.2, C41.2, C42.2, C43.2, C44.2, C45.2, C46.2, C47.2, C48.2, C49.2, C50.2, C51.2, C52.2, C53.1, C54.1, C56.1, C57.1, C58.2, D1.2 (A), D4.1 (K), D5.1 (K), D6.1 (K), D7.1 (K), D8.1 (K), D13.1 (K), D14.1 (K), H1.1, H2.1, H3.1, J1.A1 (GND), J1.A12 (GND), J1.B1 (GND), J1.B12 (GND), J2.6, J2.MP (MountPin), J3.6, J3.7, J3.8, J3.9, J3.10, Q3.1 (S), Q3.2 (S), Q3.3 (S), Q5.1 (S), Q5.2 (S), Q5.3 (S), Q6.1 (S), Q6.2 (S), Q6.3 (S), R1.2, R5.2, R6.2, R7.2, R26.1, R28.1, R41.1, R43.1, R46.1, R56.1, R57.1, R72.1, SW1.2 (B), SW2.2 (B), U1.11 (GND), U2.2 (GND), U2.3 (GND), U2.7 (GND), U2.9 (EPAD), U4.10 (PSYS), U4.27 (PGND), U4.33 (PAD), U5.1 (GND), U5.2 (GND), U5.42 (GND), U5.43 (GND), U5.46 (GND), U5.47 (GND), U5.48 (GND), U5.49 (GND), U5.50 (GND), U5.51 (GND), U5.52 (GND), U5.53 (GND), U5.54 (GND), U5.55 (GND), U5.56 (GND), U5.57 (GND), U5.58 (GND), U5.59 (GND), U5.60 (GND), U5.61 (GND), U5.62 (GND), U5.63 (GND), U5.64 (GND), U5.65 (GND), U6.1 (GND), U6.2 (GND), U6.3 (GND), U6.7 (GND), U7.3 (GND)
GNDPWR: BT4.2 (-), C11.2, C12.2, C17.2, C19.2, C20.2, C23.2, C24.2, C25.2, C26.2, D3.2 (A2), R18.1, R20.1, R29.2, R32.2, TH1.2, U3.9 (VSS), U3.23 (CTRC), U3.24 (CTRD)
unnamed: C21.1, Q2.1 (S), Q2.2 (S), Q2.3 (S), R20.4, R25.1
unnamed: C21.2, C22.1
unnamed: C27.1, R33.1
unnamed: C34.1, R34.3, R35.2
unnamed: C35.1, R34.2, R36.2
unnamed: C46.1, C55.1, R37.3, R38.2
unnamed: C49.1, R52.1
unnamed: C52.1, R53.1
unnamed: C55.2, R37.2, R39.2
unnamed: D2.2 (A), R24.2, R27.1
unnamed: D4.2 (A), R59.2
unnamed: D5.2 (A), R60.2
unnamed: D6.2 (A), R61.2
unnamed: D7.2 (A), R62.2
unnamed: D8.2 (A), R63.2
unnamed: D9.2 (A), R66.2
unnamed: D10.2 (A), R67.2
unnamed: D11.2 (A), R68.2
unnamed: D12.2 (A), R69.2
unnamed: D13.2 (A), R70.2
unnamed: D14.2 (A), R11.1
unnamed: J1.S1 (SHIELD), R1.1
unnamed: J1.A4 (VBUS), J1.A9 (VBUS), J1.B4 (VBUS), J1.B9 (VBUS), Q1.1 (S), Q1.2 (S), Q1.3 (S), R2.1, R4.2
unnamed: J4.1, U5.22 (IO18)
unnamed: J4.2, U5.21 (IO17)
unnamed: Q1.4 (G), R3.2, R4.1
unnamed: Q2.5 (D), Q3.5 (D)
unnamed: C37.1, Q4.5 (D), R34.1
unnamed: Q8.5 (D), R37.4
unnamed: R20.2, R21.1
unnamed: R20.3, R22.1
unnamed: R55.1, R56.2
unnamed: R3.1, U1.10 (GATE)
unnamed: R5.1, U1.9 (ISET)
unnamed: C1.1, R2.2, U1.1 (VIN)
unnamed: R6.1, R7.1, U1.8 (VSET)
unnamed: R9.2, U2.1 (SENSE+)
unnamed: R9.3, U2.8 (SENSE-)
unnamed: C12.1, U3.2 (AVDD)
unnamed: C11.1, R19.2, TP1.1, U3.1 (VDD), U3.20 (CCFG)
unnamed: R23.1, U3.13 (CHG)
unnamed: R24.1, U3.12 (DSG)
unnamed: R29.1, U3.17 (OCDP)
unnamed: R31.2, TH1.1, U3.18 (TS)
unnamed: R31.1, U3.19 (VTB)
unnamed: R36.1, U4.2 (ACN)
unnamed: R35.1, U4.3 (ACP)
unnamed: R45.1, R46.2, TP2.1, U4.14 (CMPIN)
unnamed: R64.1, U5.5 (IO1)
unnamed: R65.1, U5.6 (IO2)
unnamed: R71.1, R72.2, U7.5 (EN)
unnamed: R13.1, R14.1, R57.2, U7.6 (FB)
unnamed: R12.1, U7.4 (PG)
VDD: C2.1, C3.1, C4.1, J3.1, J3.2, J3.3, J3.4, J3.5, R9.1, R70.1, R71.2, U7.1 (VIN)

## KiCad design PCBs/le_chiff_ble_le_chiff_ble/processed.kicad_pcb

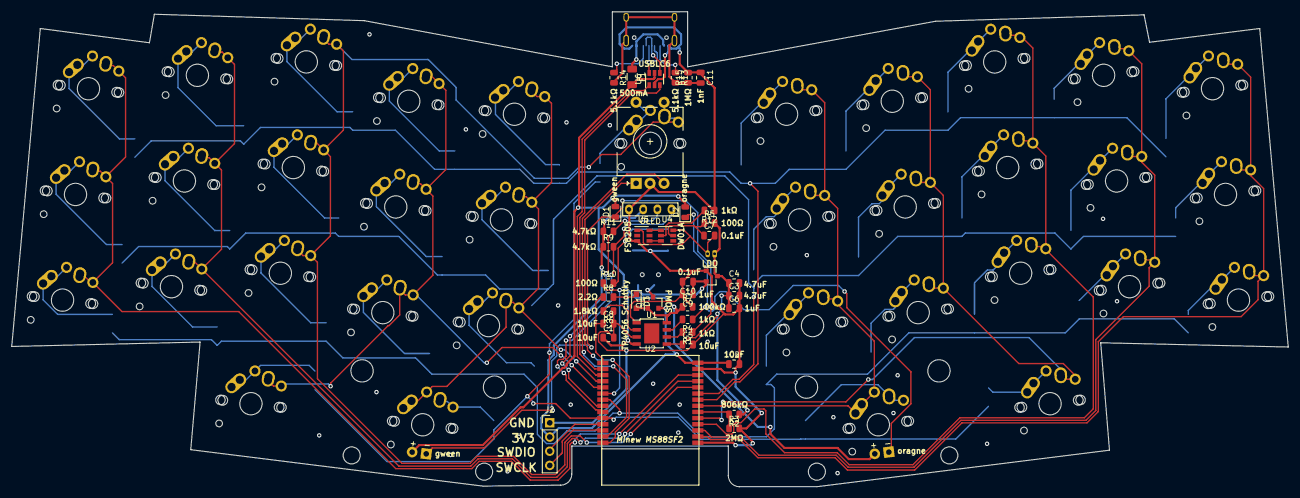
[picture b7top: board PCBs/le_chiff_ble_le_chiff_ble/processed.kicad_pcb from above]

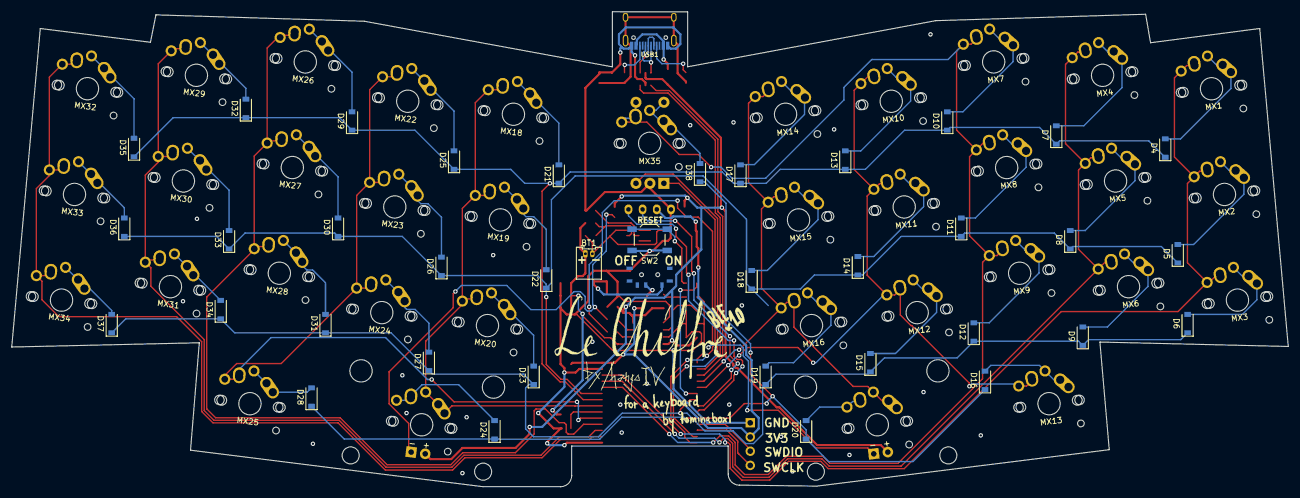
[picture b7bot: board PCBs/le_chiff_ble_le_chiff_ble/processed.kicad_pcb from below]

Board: 2 copper layers, 228.4 x 85.0 mm, 114 parts (39 on the bottom side), 84 nets.

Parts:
BT1: Battery_Cell; Molex_PicoBlade_53048-0210_1x02_P1.25mm_Horizontal
C1, C2, C5, C8: 10uF; C_0805_2012Metric
C3, C4: 4.7uF; C_0805_2012Metric
C6, C9: 1uF; C_0805_2012Metric
C7: 0.1uF; C_0805_2012Metric
C10: 100nF; C_0805_2012Metric
C11: 1nF; C_0805_2012Metric
D1: gween; D_0805_2012Metric
D2: oragne; D_0805_2012Metric
D3: D_Schottky_Small; D_SOD-323_HandSoldering
D4, D5, D6, D7, D8, D9, D10, D11, D12, D13, D14, D15, D16, D17, D18, D19, D20, D21, D22, D23, D24, D25, D26, D27, D28, D29, D30, D31, D32, D33, D34, D35, D36, D37, D38: D_Small; D_SOD-123
F1: 500mA; Fuse_1206_3216Metric
J2: BL_CONN; PinHeader_1x04_P2.54mm_Vertical
MX1, MX2, MX3, MX4, MX5, MX6, MX7, MX8, MX9, MX10, MX11, MX12, MX13, MX14, MX15, MX16, MX18, MX19, MX20, MX22, MX23, MX24, MX25, MX26, MX27, MX28, MX29, MX30, MX31, MX32, MX33, MX34, MX35: MX_LED; MX-Alps-Choc-1U-NoLED
MX17, MX21: MX_LED; MX-Alps-Choc-2U-StabFlip
OL1: OLED; OLED_1side
Q1: AO3401A; SOT-23
R1, R4, R12: 1k; R_0805_2012Metric
R2: 806k; R_0805_2012Metric
R3: 2M; R_0805_2012Metric
R5, R10: 100; R_0805_2012Metric
R6: 1.8k; R_0805_2012Metric
R7: 100k; R_0805_2012Metric
R8: 2R2; R_0805_2012Metric
R9, R11: 4.7k; R_0805_2012Metric
R13, R14: 5.1k; R_0805_2012Metric
R15: 1M; R_0805_2012Metric
SW1: ON_OFF; switch_MSK-12C02_smd
SW2: SW_RESET; SW_SPST_TL3342
SW3: Rotary_Encoder_Switch; RotaryEncoder_EC11-no-legs
U1: TP4056; TP4056_SOP-8-PP
U2: MS88SF2; MINEW_MS88SF2
U3: XC6206PxxxMR-Regulator_Linear; SOT-23
U4: DW01A; SOT-23-6
U5: FS8205; SOT-23-6
U6: USBLC6-2SC6; SOT-23-6
USB1: HRO-TYPE-C-31-M-12; HRO-TYPE-C-31-M-12-Assembly

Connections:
+3V3: C2.1, J2.2, OL1.3, Q1.2, R9.1, R11.1, U2.14
Earth: C11.2, R13.2, R14.2, R15.1, USB1.13
GND: C1.2, C2.2, C3.2, C4.2, C5.2, C6.2, C8.2, C9.2, C10.2, C11.1, J2.1, OL1.4, R3.2, R6.1, R7.2, R12.1, R15.2, SW2.1, SW3.C, U1.1, U1.3, U2.1, U2.13, U3.1, U5.3, U6.2, USB1.1, USB1.12
unnamed: BT1.2, C7.2, U4.6, U5.1
unnamed: C7.1, R5.1, U4.5
unnamed: C8.1, R8.1, U2.15
unnamed: D1.1, MX17.4, R1.1
unnamed: D2.1, MX21.4, R4.1
unnamed: D3.1, R8.2
unnamed: D4.2, MX1.2
unnamed: D5.2, MX2.2
unnamed: D6.2, MX3.2
unnamed: D7.2, MX4.2
unnamed: D8.2, MX5.2
unnamed: D9.2, MX6.2
unnamed: D10.2, MX7.2
unnamed: D11.2, MX8.2
unnamed: D12.2, MX9.2
unnamed: D13.2, MX10.2
unnamed: D14.2, MX11.2
unnamed: D15.2, MX12.2
unnamed: D16.2, MX13.2
unnamed: D17.2, MX14.2
unnamed: D18.2, MX15.2
unnamed: D19.2, MX16.2
unnamed: D20.2, MX17.2
unnamed: D21.2, MX18.2
unnamed: D22.2, MX19.2
unnamed: D23.2, MX20.2
unnamed: D24.2, MX21.2
unnamed: D25.2, MX22.2
unnamed: D26.2, MX23.2
unnamed: D27.2, MX24.2
unnamed: D28.2, MX25.2
unnamed: D29.2, MX26.2
unnamed: D30.2, MX27.2
unnamed: D31.2, MX28.2
unnamed: D32.2, MX29.2
unnamed: D33.2, MX30.2
unnamed: D34.2, MX31.2
unnamed: D35.2, MX32.2
unnamed: D36.2, MX33.2
unnamed: D37.2, MX34.2
unnamed: F1.1, USB1.2, USB1.11
unnamed: Q1.3, SW1.2
unnamed: R1.2, U1.6
unnamed: R4.2, U1.7
unnamed: R6.2, U1.2
unnamed: R10.2, SW2.2
unnamed: R12.2, U4.2
unnamed: U4.1, U5.6
unnamed: U4.3, U5.4
cc1: R14.1, USB1.4
cc2: R13.1, USB1.10
col0: MX1.1, MX2.1, MX3.1, U2.12
col1: MX4.1, MX5.1, MX6.1, U2.11
col2: MX7.1, MX8.1, MX9.1, MX35.1, SW3.S1, U2.10
col3: MX10.1, MX11.1, MX12.1, MX13.1, U2.19
col4: MX14.1, MX15.1, MX16.1, MX17.1, U2.18
col5: MX18.1, MX19.1, MX20.1, MX21.1, U2.7
col6: MX22.1, MX23.1, MX24.1, MX25.1, U2.5
col7: MX26.1, MX27.1, MX28.1, U2.4
col8: MX29.1, MX30.1, MX31.1, U2.3
col9: MX32.1, MX33.1, MX34.1, U2.2
d+: U2.17, U6.1
d-: U2.16, U6.3
dbus+: U6.6, USB1.6, USB1.8
dbus-: U6.4, USB1.5, USB1.7
encA: SW3.A, U2.28
encB: SW3.B, U2.27
encswrow: D38.2, MX35.2, SW3.S2
regbat: C9.1, C10.1, SW1.1, U3.2
reset: R10.1, U2.20
row0: D4.1, D7.1, D10.1, D13.1, D17.1, D21.1, D25.1, D29.1, D32.1, D35.1, U2.8
row1: D5.1, D8.1, D11.1, D14.1, D18.1, D22.1, D26.1, D30.1, D33.1, D36.1, U2.9
row2: D6.1, D9.1, D12.1, D15.1, D19.1, D23.1, D27.1, D31.1, D34.1, D37.1, U2.21
row3: D16.1, D20.1, D24.1, D28.1, D38.1, U2.24
scl: OL1.2, R11.2, U2.22
sda: OL1.1, R9.2, U2.23
swclk: J2.4, U2.26
swdio: J2.3, U2.25
vbat: BT1.1, C3.1, C4.1, C5.1, C6.1, R2.1, R5.2, U1.5, U3.3
vbus: C1.1, D1.2, D2.2, D3.2, F1.2, MX17.3, MX21.3, Q1.1, R7.1, U1.4, U1.8, U6.5
vsense: R2.2, R3.1, U2.6
